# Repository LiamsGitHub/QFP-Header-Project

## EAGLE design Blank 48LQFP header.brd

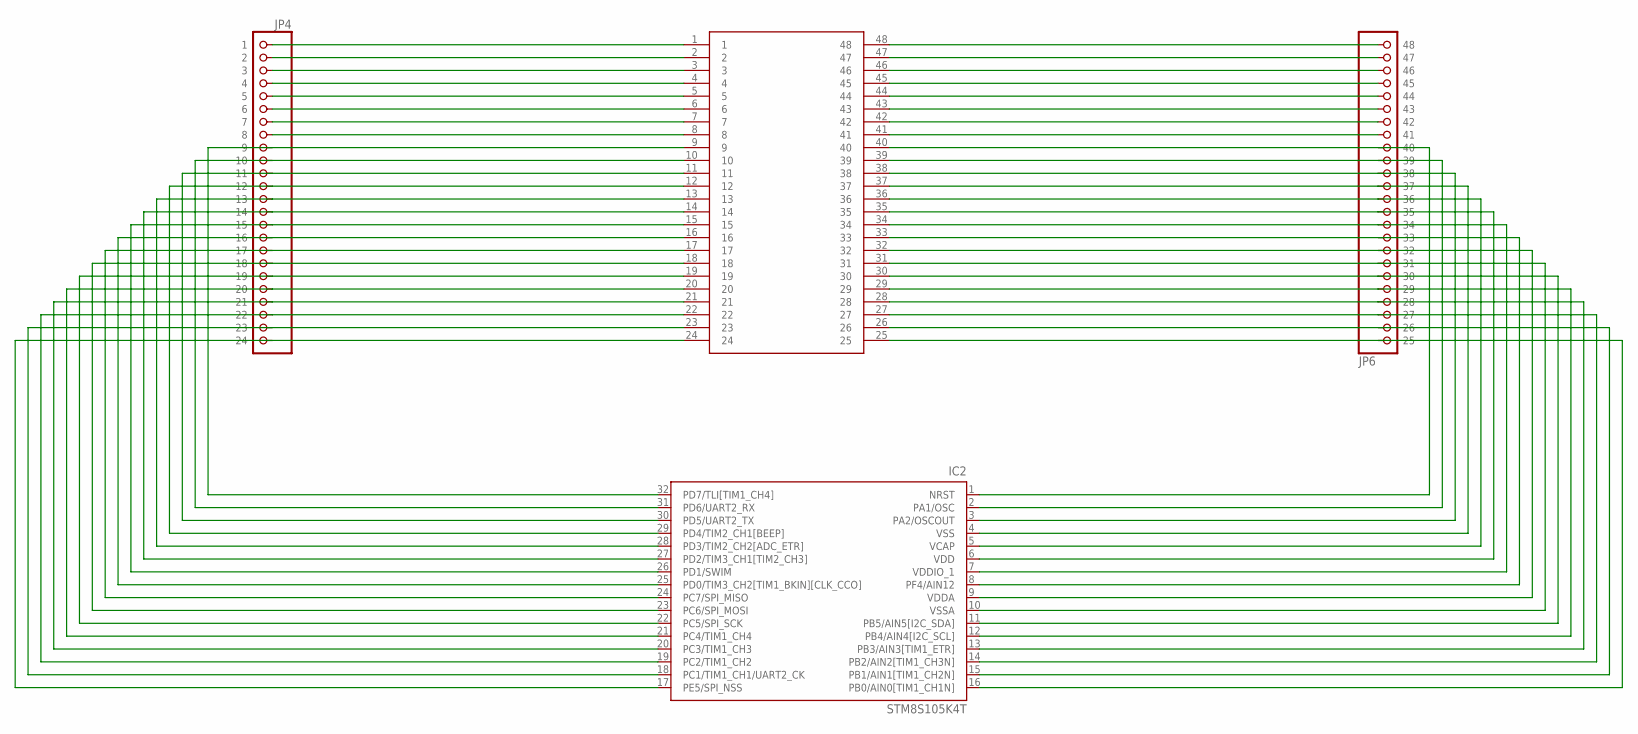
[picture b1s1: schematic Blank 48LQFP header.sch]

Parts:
IC2: STM8S105K4T; LQFP32-7X7
JP4: PINHD-1X241X24_PINS_1_TO_24; 1X24
JP6: PINHD-1X24-25TO48; 1X24
U$1: GENERICLQFP48; TQFP48

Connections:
unnamed: JP4.1, U$1.1
unnamed: IC2.9 (VDDA), JP6.8 (32), U$1.32
unnamed: IC2.1 (NRST), JP6.16 (40), U$1.40
unnamed: IC2.3 (PA2/OSCOUT), JP6.14 (38), U$1.38
unnamed: JP4.2, U$1.2
unnamed: JP4.3, U$1.3
unnamed: JP4.4, U$1.4
unnamed: JP4.5, U$1.5
unnamed: JP4.6, U$1.6
unnamed: JP6.17 (41), U$1.41
unnamed: IC2.4 (VSS), JP6.13 (37), U$1.37
unnamed: JP4.7, U$1.7
unnamed: JP4.8, U$1.8
unnamed: IC2.31 (PD6/UART2_RX), JP4.10, U$1.10
unnamed: IC2.24 (PC7/SPI_MISO), JP4.17, U$1.17
unnamed: IC2.29 (PD4/TIM2_CH1[BEEP]), JP4.12, U$1.12
unnamed: IC2.28 (PD3/TIM2_CH2[ADC_ETR]), JP4.13, U$1.13
unnamed: IC2.27 (PD2/TIM3_CH1[TIM2_CH3]), JP4.14, U$1.14
unnamed: IC2.26 (PD1/SWIM), JP4.15, U$1.15
unnamed: IC2.25 (PD0/TIM3_CH2[TIM1_BKIN][CLK_CCO]), JP4.16, U$1.16
unnamed: IC2.30 (PD5/UART2_TX), JP4.11, U$1.11
unnamed: IC2.22 (PC5/SPI_SCK), JP4.19, U$1.19
unnamed: IC2.21 (PC4/TIM1_CH4), JP4.20, U$1.20
unnamed: IC2.20 (PC3/TIM1_CH3), JP4.21, U$1.21
unnamed: IC2.19 (PC2/TIM1_CH2), JP4.22, U$1.22
unnamed: IC2.18 (PC1/TIM1_CH1/UART2_CK), JP4.23, U$1.23
unnamed: IC2.17 (PE5/SPI_NSS), JP4.24, U$1.24
unnamed: IC2.32 (PD7/TLI[TIM1_CH4]), JP4.9, U$1.9
unnamed: IC2.16 (PB0/AIN0[TIM1_CH1N]), JP6.1 (25), U$1.25
unnamed: IC2.15 (PB1/AIN1[TIM1_CH2N]), JP6.2 (26), U$1.26
unnamed: IC2.14 (PB2/AIN2[TIM1_CH3N]), JP6.3 (27), U$1.27
unnamed: IC2.13 (PB3/AIN3[TIM1_ETR]), JP6.4 (28), U$1.28
unnamed: IC2.12 (PB4/AIN4[I2C_SCL]), JP6.5 (29), U$1.29
unnamed: IC2.11 (PB5/AIN5[I2C_SDA]), JP6.6 (30), U$1.30
unnamed: IC2.10 (VSSA), JP6.7 (31), U$1.31
unnamed: IC2.5 (VCAP), JP6.12 (36), U$1.36
unnamed: IC2.8 (PF4/AIN12), JP6.9 (33), U$1.33
unnamed: IC2.7 (VDDIO_1), JP6.10 (34), U$1.34
unnamed: IC2.23 (PC6/SPI_MOSI), JP4.18, U$1.18
unnamed: JP6.24 (48), U$1.48
unnamed: JP6.23 (47), U$1.47
unnamed: JP6.22 (46), U$1.46
unnamed: JP6.21 (45), U$1.45
unnamed: JP6.20 (44), U$1.44
unnamed: JP6.19 (43), U$1.43
unnamed: JP6.18 (42), U$1.42
unnamed: IC2.6 (VDD), JP6.11 (35), U$1.35
unnamed: IC2.2 (PA1/OSC), JP6.15 (39), U$1.39

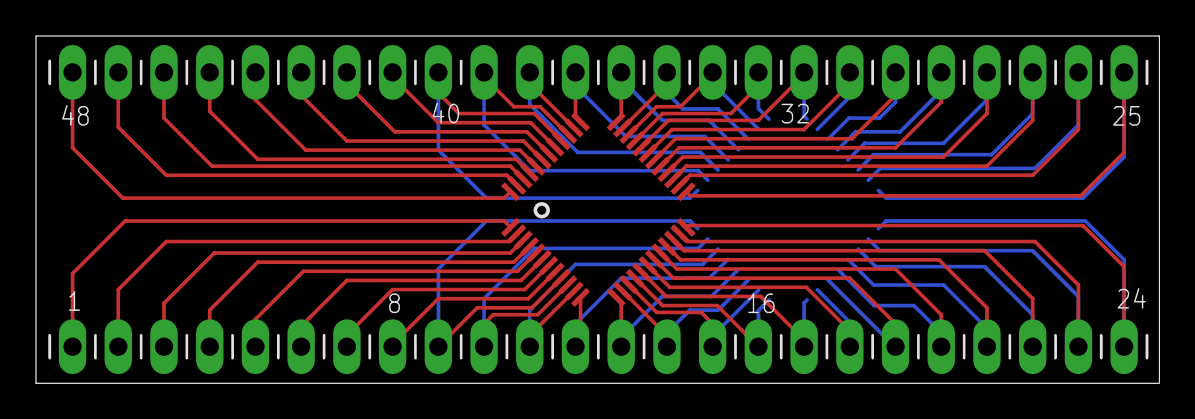
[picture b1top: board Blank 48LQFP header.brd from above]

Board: 2 copper layers, 62.4 x 19.3 mm, 4 parts (1 on the bottom side), 48 nets.

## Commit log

2014-08-14 First sync
